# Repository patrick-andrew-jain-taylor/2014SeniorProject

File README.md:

2014SeniorProject
=================

Will contain all source files for our Glasses project

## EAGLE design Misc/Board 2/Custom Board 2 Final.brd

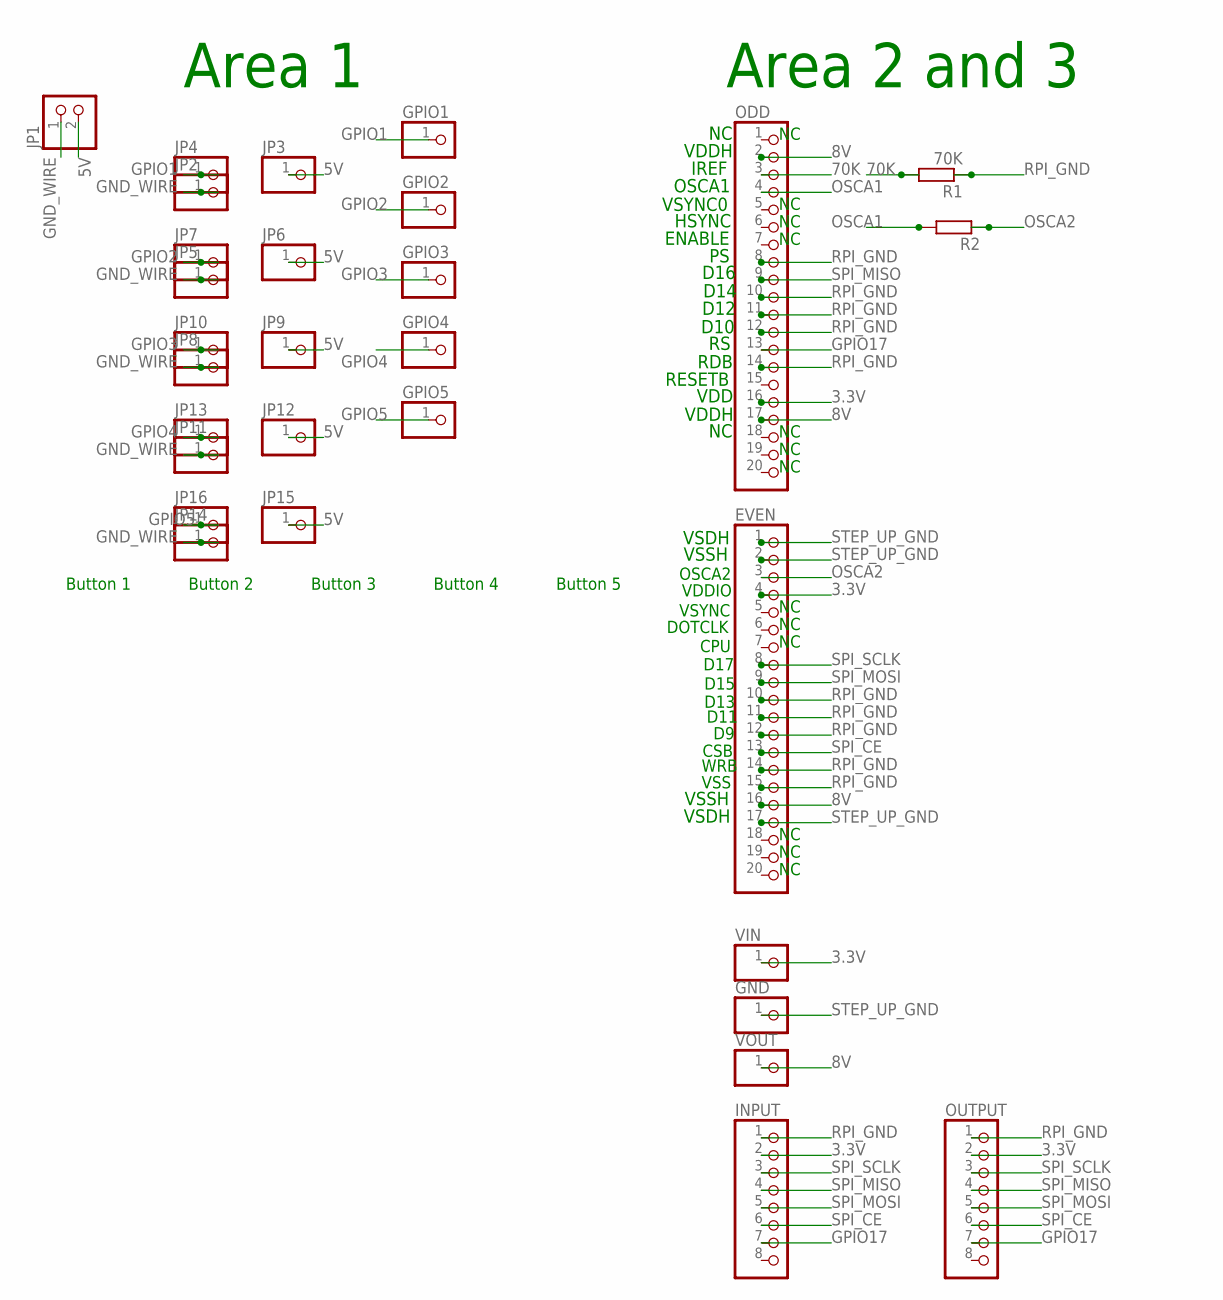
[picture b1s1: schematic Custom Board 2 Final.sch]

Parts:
EVEN: PINHD-1X20; 1X20
GND: PINHD-1X1; 1X01
GPIO1, GPIO2, GPIO3, GPIO4, GPIO5: PINHD-1X1; 1X01
INPUT: PINHD-1X8; 1X08
JP1: PINHD-1X2; 1X02
JP2, JP3, JP4, JP5, JP6, JP7, JP8, JP9, JP10, JP11, JP12, JP13, JP14, JP15, JP16: PINHD-1X1; 1X01
ODD: PINHD-1X20; 1X20
OUTPUT: PINHD-1X8; 1X08
R1: 70K; 0204/7
R2: R-EU_0204/7; 0204/7
VIN: PINHD-1X1; 1X01
VOUT: PINHD-1X1; 1X01

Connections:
3.3V: EVEN.4, INPUT.2, ODD.16, OUTPUT.2, VIN.1
5V: JP1.2, JP3.1, JP6.1, JP9.1, JP12.1, JP15.1
8V: EVEN.16, ODD.2, ODD.17, VOUT.1
70K: ODD.3, R1.2
GND_WIRE: JP1.1, JP2.1, JP5.1, JP8.1, JP11.1, JP14.1
GPIO1: GPIO1.1, JP4.1
GPIO2: GPIO2.1, JP7.1
GPIO3: GPIO3.1, JP10.1
GPIO4: GPIO4.1, JP13.1
GPIO5: GPIO5.1, JP16.1
GPIO17: INPUT.7, ODD.13, OUTPUT.7
OSCA1: ODD.4, R2.2
OSCA2: EVEN.3, R2.1
RPI_GND: EVEN.10, EVEN.11, EVEN.12, EVEN.14, EVEN.15, INPUT.1, ODD.8, ODD.10, ODD.11, ODD.12, ODD.14, OUTPUT.1, R1.1
SPI_CE: EVEN.13, INPUT.6, OUTPUT.6
SPI_MISO: INPUT.4, ODD.9, OUTPUT.4
SPI_MOSI: EVEN.9, INPUT.5, OUTPUT.5
SPI_SCLK: EVEN.8, INPUT.3, OUTPUT.3
STEP_UP_GND: EVEN.1, EVEN.2, EVEN.17, GND.1

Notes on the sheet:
Area 1
Area 2 and 3
VSDH
VDDH
VSSH
IREF
OSCA1
VSYNC0
HSYNC
ENABLE
D16
D14
D12
D10
RDB
RESETB
VDD
OSCA2
VDDIO
VSYNC
DOTCLK
CPU
D17
D15
D13
D11
CSB
WRB
VSS
Button 1
Button 2
Button 3
Button 4
Button 5

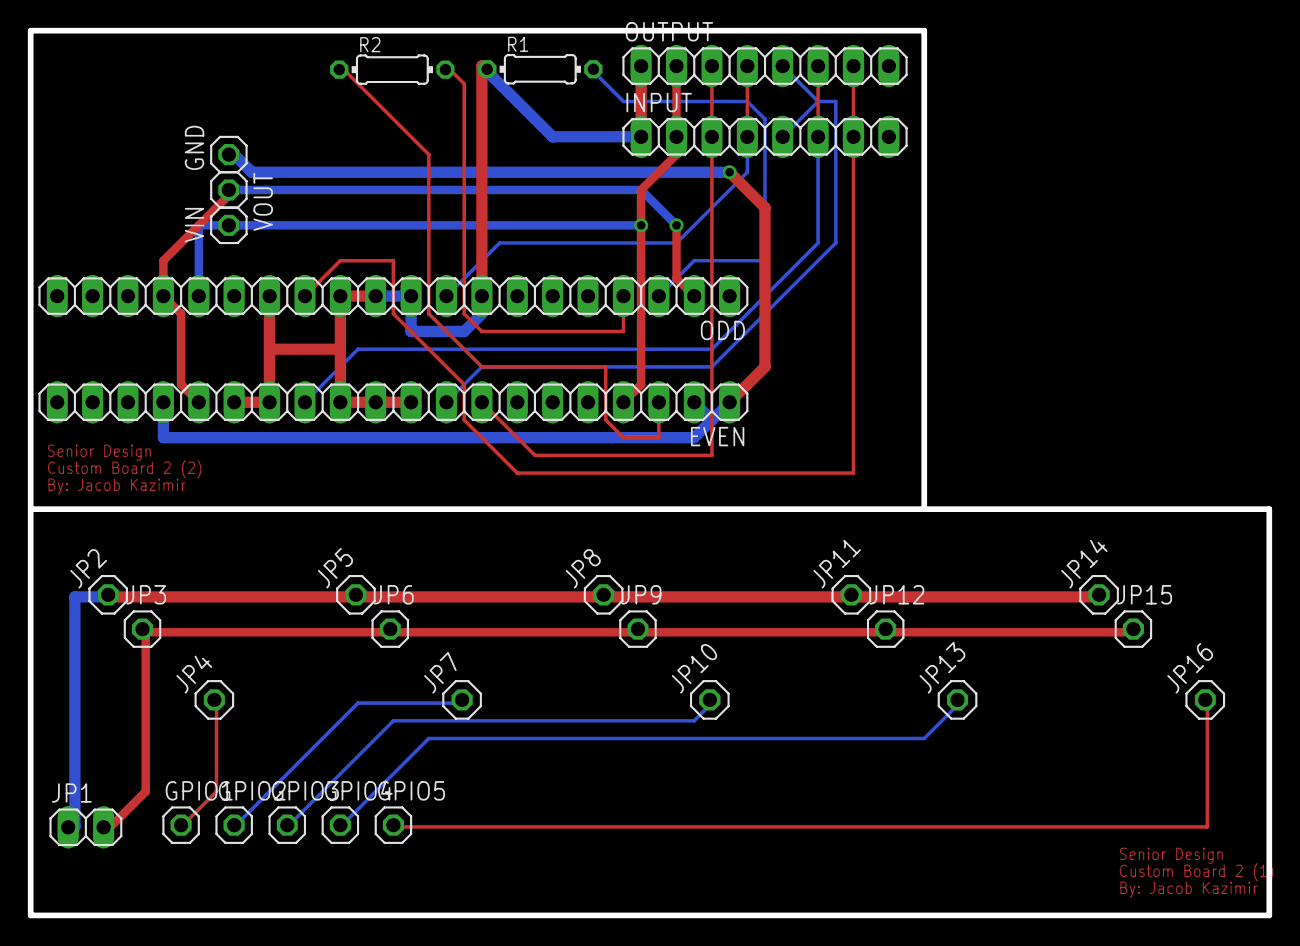
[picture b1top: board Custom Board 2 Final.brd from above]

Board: 2 copper layers, 88.9 x 63.5 mm, 30 parts (0 on the bottom side), 19 nets.

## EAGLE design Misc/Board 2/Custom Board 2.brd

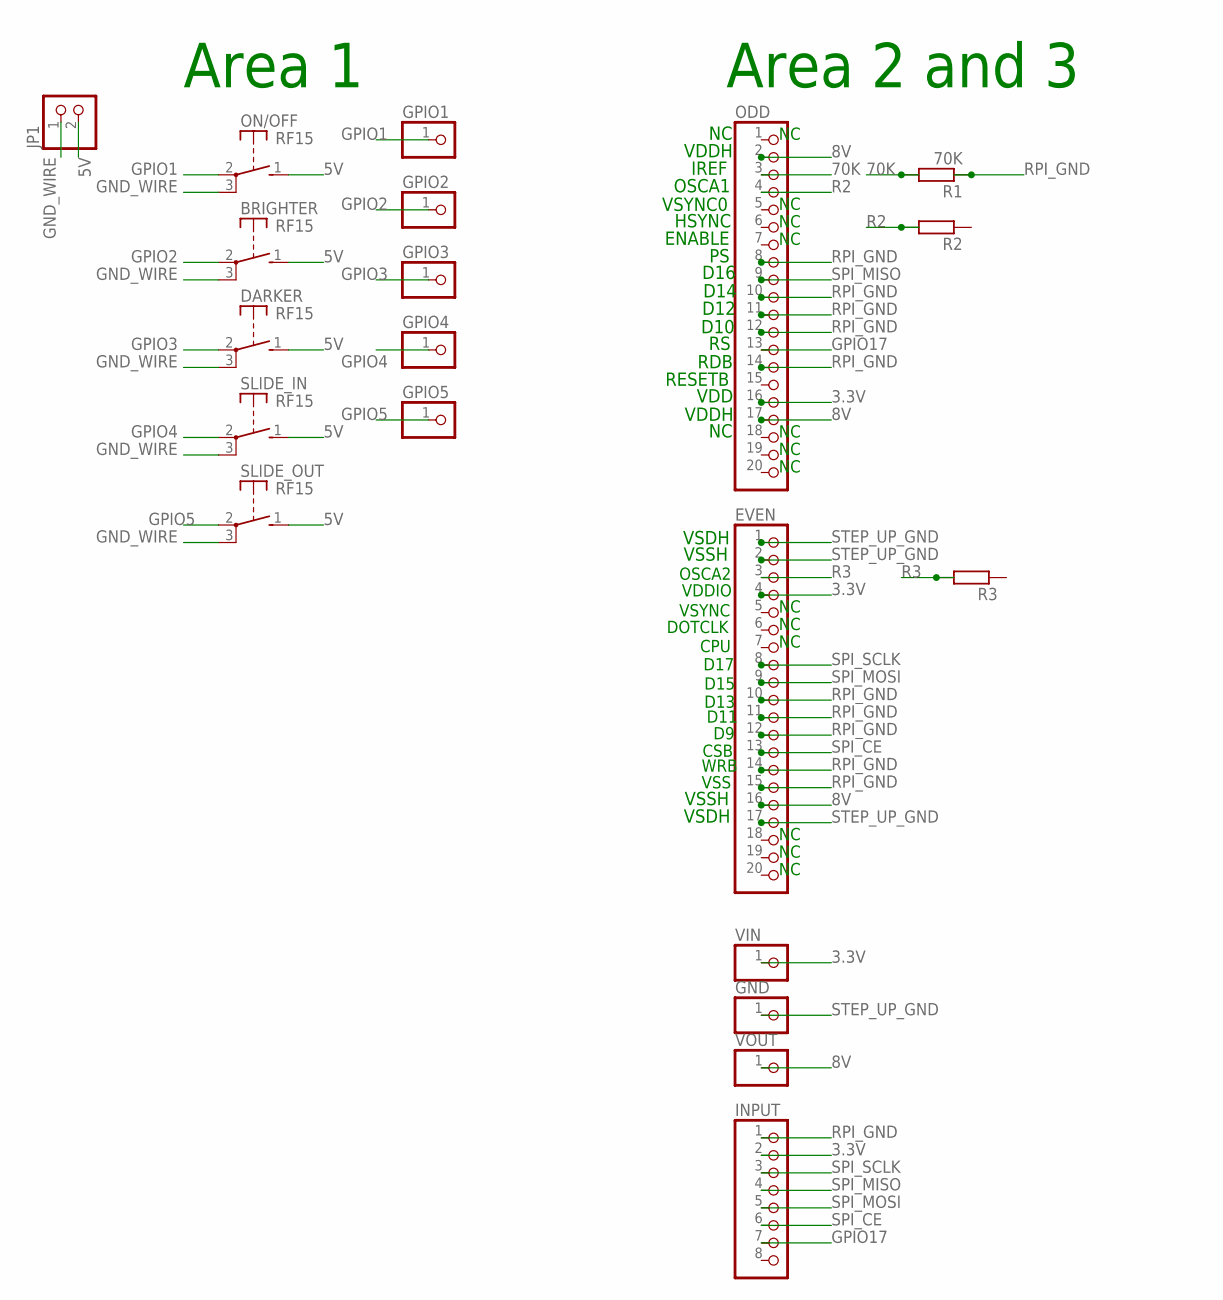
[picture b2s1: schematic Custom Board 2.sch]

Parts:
BRIGHTER: RF15
DARKER: RF15
EVEN: PINHD-1X20; 1X20
GND: PINHD-1X1; 1X01
GPIO1, GPIO2, GPIO3, GPIO4, GPIO5: PINHD-1X1; 1X01
INPUT: PINHD-1X8; 1X08
JP1: PINHD-1X2; 1X02
ODD: PINHD-1X20; 1X20
ON/OFF: RF15
R1: 70K; 0204/7
R2, R3: R-EU_0204/7; 0204/7
SLIDE_IN: RF15
SLIDE_OUT: RF15
VIN: PINHD-1X1; 1X01
VOUT: PINHD-1X1; 1X01

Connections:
3.3V: EVEN.4, INPUT.2, ODD.16, VIN.1
5V: BRIGHTER.1 (S), DARKER.1 (S), JP1.2, ON/OFF.1 (S), SLIDE_IN.1 (S), SLIDE_OUT.1 (S)
8V: EVEN.16, ODD.2, ODD.17, VOUT.1
70K: ODD.3, R1.2
GND_WIRE: BRIGHTER.3, DARKER.3, JP1.1, ON/OFF.3, SLIDE_IN.3, SLIDE_OUT.3
GPIO1: GPIO1.1, ON/OFF.2
GPIO2: BRIGHTER.2, GPIO2.1
GPIO3: DARKER.2, GPIO3.1
GPIO4: GPIO4.1, SLIDE_IN.2
GPIO5: GPIO5.1, SLIDE_OUT.2
GPIO17: INPUT.7, ODD.13
R2: ODD.4, R2.2
R3: EVEN.3, R3.2
RPI_GND: EVEN.10, EVEN.11, EVEN.12, EVEN.14, EVEN.15, INPUT.1, ODD.8, ODD.10, ODD.11, ODD.12, ODD.14, R1.1
SPI_CE: EVEN.13, INPUT.6
SPI_MISO: INPUT.4, ODD.9
SPI_MOSI: EVEN.9, INPUT.5
SPI_SCLK: EVEN.8, INPUT.3
STEP_UP_GND: EVEN.1, EVEN.2, EVEN.17, GND.1

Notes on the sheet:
Area 1
Area 2 and 3
VSDH
VDDH
VSSH
IREF
OSCA1
VSYNC0
HSYNC
ENABLE
D16
D14
D12
D10
RDB
RESETB
VDD
OSCA2
VDDIO
VSYNC
DOTCLK
CPU
D17
D15
D13
D11
CSB
WRB
VSS

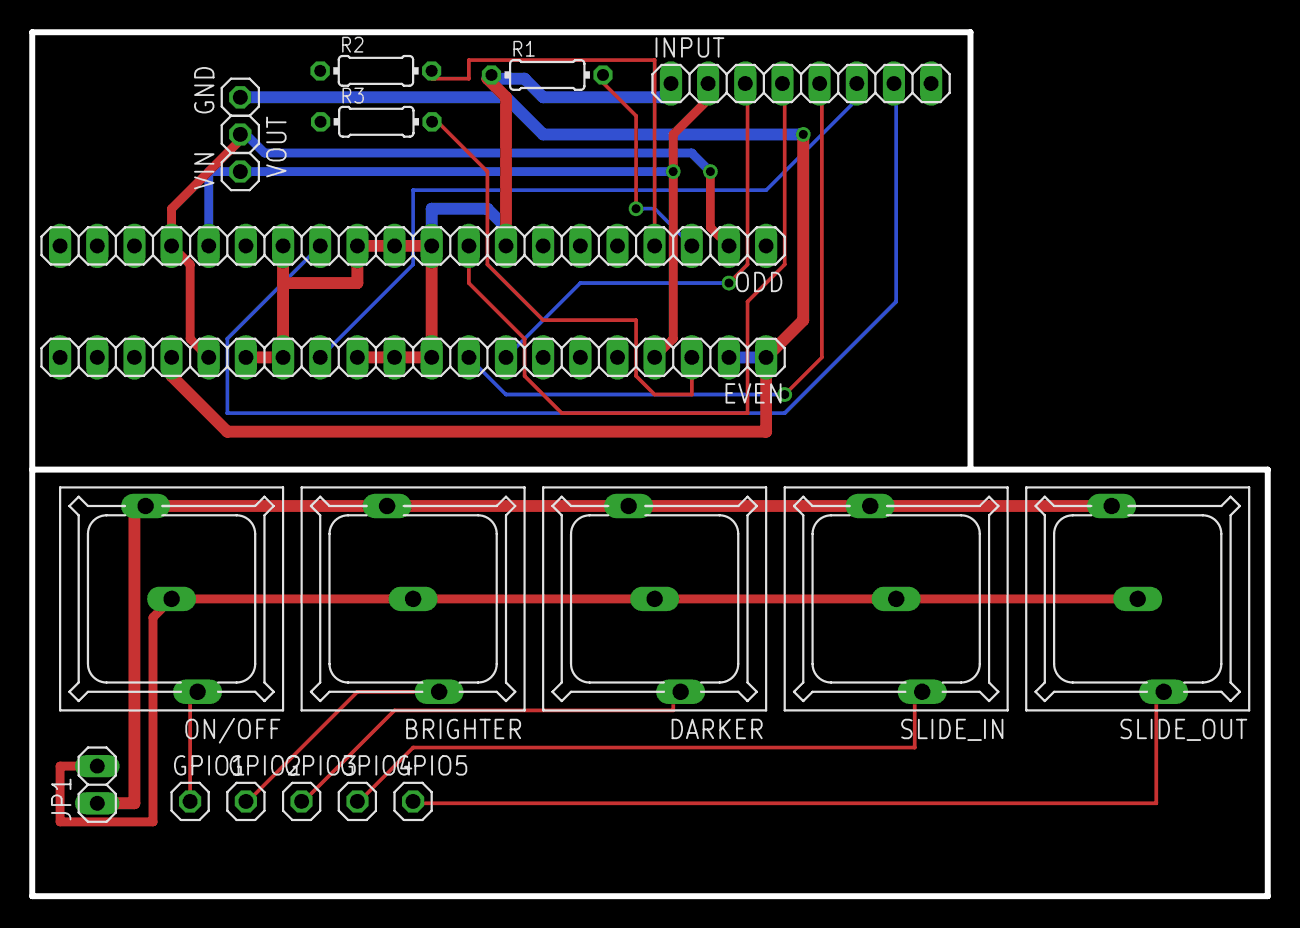
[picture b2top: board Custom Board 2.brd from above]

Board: 2 copper layers, 84.5 x 59.1 mm, 20 parts (0 on the bottom side), 19 nets.

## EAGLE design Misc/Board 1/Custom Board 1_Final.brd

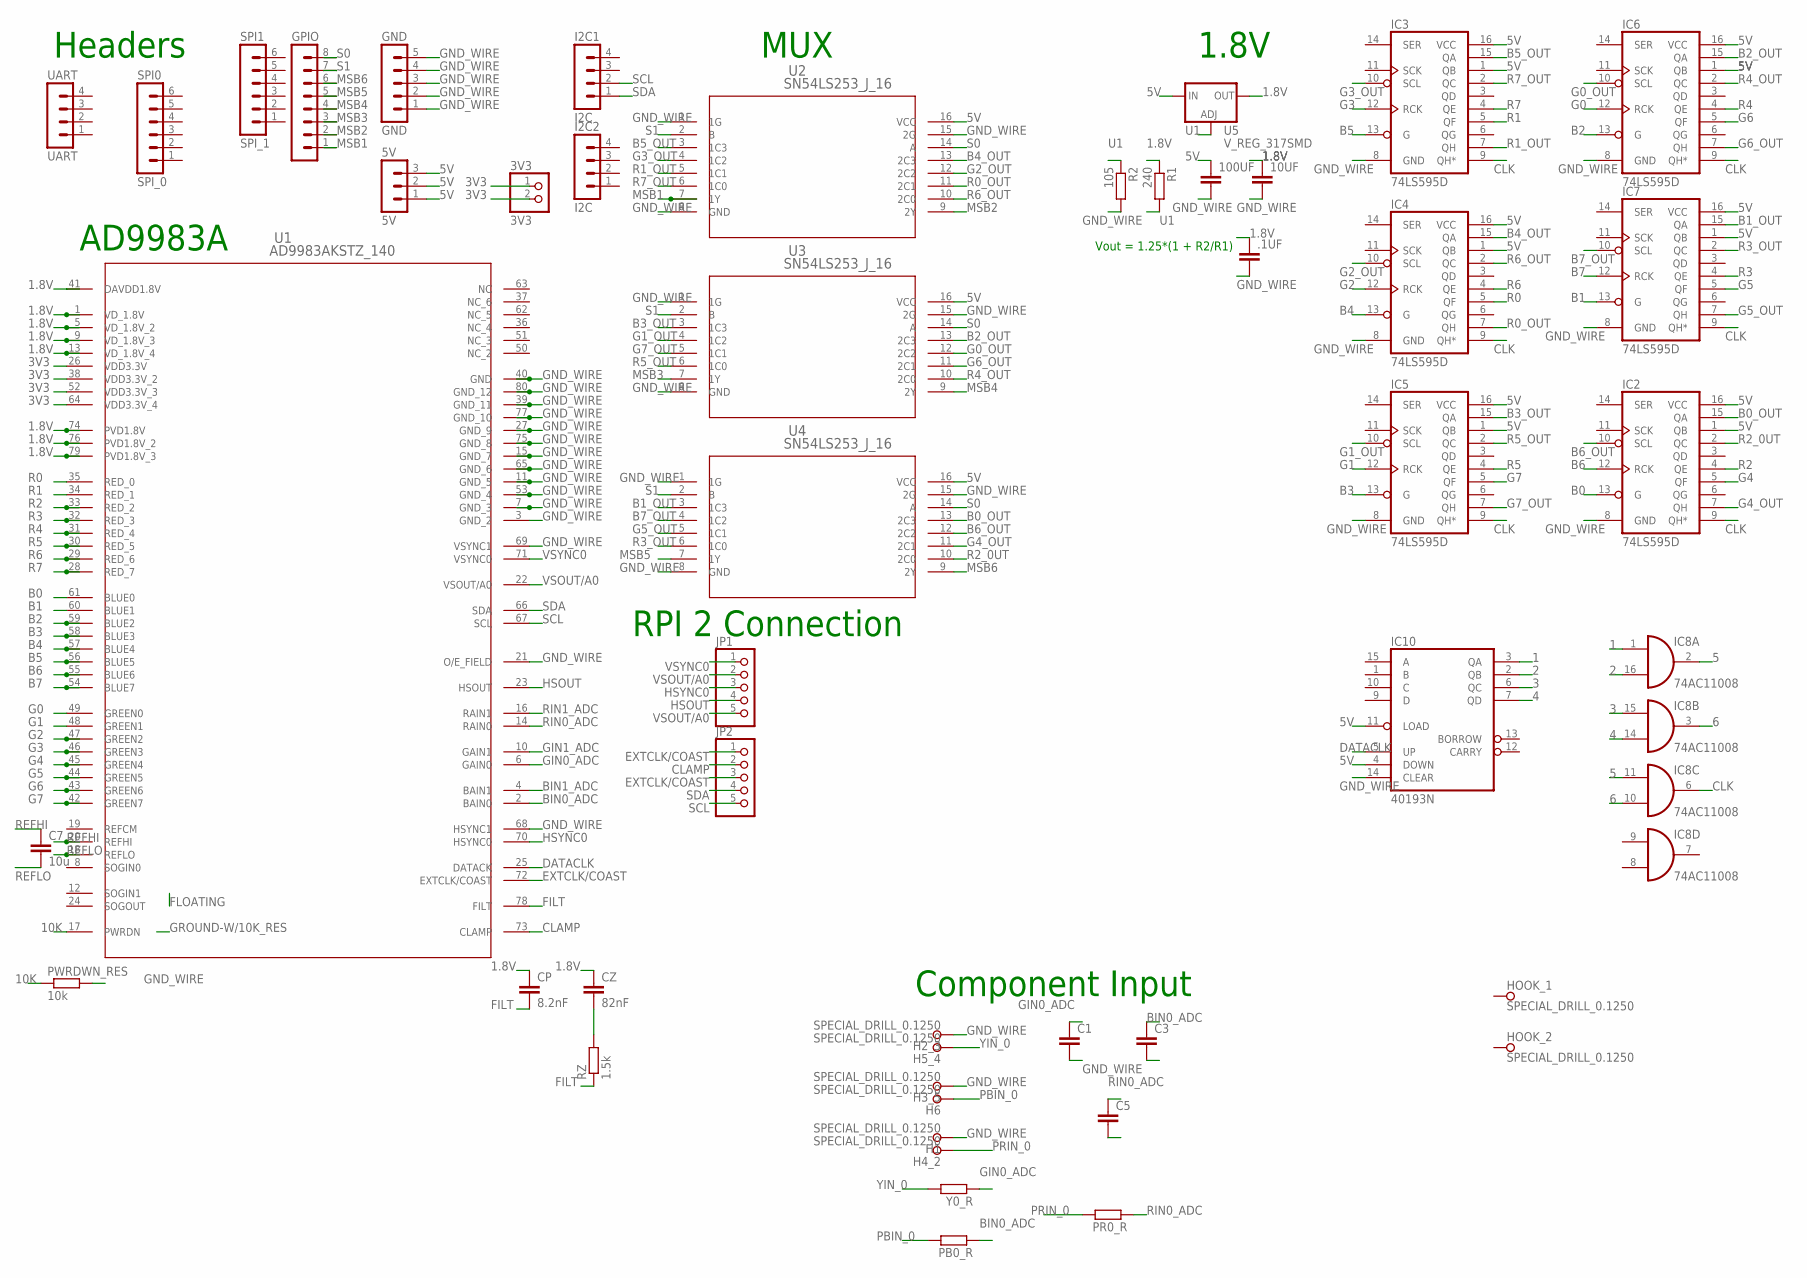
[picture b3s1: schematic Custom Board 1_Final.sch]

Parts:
3V3: 3V3; 1X02
5V: 5V; MA03-1
10UF, 100UF, .1UF: C2.5/5; C2.5-5
C1, C3, C5: C2.5/5; C2.5-5
C7: 10u; C2.5-5
CP: 8.2nF; C2.5-5
CZ: 82nF; C2.5-5
GND: GND; MA05-1
GPIO: MA08-1
H1, H2_3, H3_5, H4_2, H5_4, H6: SPECIAL_DRILL_0.1250; PAD_0.1250
HOOK_1, HOOK_2: SPECIAL_DRILL_0.1250; PAD_0.1250
I2C1, I2C2: I2C; MA04-1
IC2, IC3, IC4, IC5, IC6, IC7: 74LS595D; SO16
IC8: 74AC11008; DIL16
IC10: 40193N; DIL16
JP1, JP2: PINHD-1X5; 1X05
PB0_R: R0204/7; 0204/7
PR0_R: R0204/7; 0204/7
PWRDWN_RES: 10k; 0204/7
R1: 240; 0204/7
R2: 105; 0204/7
RZ: 1.5k; 0204/7
SPI0: SPI_0; MA06-1
SPI1: SPI_1; MA06-1
U1: AD9983AKSTZ_140; ST_80_2
U2, U3, U4: SN54LS253_J_16; J16
U5: V_REG_317SMD; SOT223
UART: UART; MA04-1
Y0_R: R0204/7; 0204/7

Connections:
1: IC8.1 (I0), IC10.3 (QA)
1.8V: 10UF.1, .1UF.1, CP.1, CZ.1, R1.1, U1.1 (VD_1.8V), U1.5 (VD_1.8V_2), U1.9 (VD_1.8V_3), U1.13 (VD_1.8V_4), U1.41 (DAVDD1.8V), U1.74 (PVD1.8V), U1.76 (PVD1.8V_2), U1.79 (PVD1.8V_3), U5.2 (OUT)
2: IC8.16 (I1), IC10.2 (QB)
3: IC8.15 (I0), IC10.6 (QC)
3V3: 3V3.1, 3V3.2, U1.26 (VDD3.3V), U1.38 (VDD3.3V_2), U1.52 (VDD3.3V_3), U1.64 (VDD3.3V_4)
4: IC8.14 (I1), IC10.7 (QD)
5: IC8.2 (O), IC8.11 (I0)
5V: 5V.1, 5V.2, 5V.3, 100UF.1, IC2.1 (QB), IC2.16 (VCC), IC3.1 (QB), IC3.16 (VCC), IC4.1 (QB), IC4.16 (VCC), IC5.1 (QB), IC5.16 (VCC), IC6.1 (QB), IC6.16 (VCC), IC7.1 (QB), IC7.16 (VCC), IC10.4 (DOWN), IC10.11 (LOAD), U2.16 (VCC), U3.16 (VCC), U4.16 (VCC), U5.3 (IN)
6: IC8.3 (O), IC8.10 (I1)
10K: PWRDWN_RES.1, U1.17 (PWRDN)
B0: IC2.13 (G), U1.61 (BLUE0)
B0_OUT: IC2.15 (QA), U4.13 (2C3)
B1: IC7.13 (G), U1.60 (BLUE1)
B1_OUT: IC7.15 (QA), U4.3 (1C3)
B2: IC6.13 (G), U1.59 (BLUE2)
B2_OUT: IC6.15 (QA), U3.13 (2C3)
B3: IC5.13 (G), U1.58 (BLUE3)
B3_OUT: IC5.15 (QA), U3.3 (1C3)
B4: IC4.13 (G), U1.57 (BLUE4)
B4_OUT: IC4.15 (QA), U2.13 (2C3)
B5: IC3.13 (G), U1.56 (BLUE5)
B5_OUT: IC3.15 (QA), U2.3 (1C3)
B6: IC2.12 (RCK), U1.55 (BLUE6)
B6_OUT: IC2.10 (SCL), U4.12 (2C2)
B7: IC7.12 (RCK), U1.54 (BLUE7)
B7_OUT: IC7.10 (SCL), U4.4 (1C2)
BIN0_ADC: C3.1, PB0_R.1, U1.2 (BAIN0)
BIN1_ADC: U1.4 (BAIN1)
CLAMP: JP2.2, U1.73 (CLAMP)
CLK: IC2.9 (QH*), IC3.9 (QH*), IC4.9 (QH*), IC5.9 (QH*), IC6.9 (QH*), IC7.9 (QH*), IC8.6 (O)
DATACLK: IC10.5 (UP), U1.25 (DATACK)
EXTCLK/COAST: JP2.1, JP2.3, U1.72 (EXTCLK/COAST)
FILT: CP.2, RZ.1, U1.78 (FILT)
G0: IC6.12 (RCK), U1.49 (GREEN0)
G0_OUT: IC6.10 (SCL), U3.12 (2C2)
G1: IC5.12 (RCK), U1.48 (GREEN1)
G1_OUT: IC5.10 (SCL), U3.4 (1C2)
G2: IC4.12 (RCK), U1.47 (GREEN2)
G2_OUT: IC4.10 (SCL), U2.12 (2C2)
G3: IC3.12 (RCK), U1.46 (GREEN3)
G3_OUT: IC3.10 (SCL), U2.4 (1C2)
G4: IC2.5 (QF), U1.45 (GREEN4)
G4_OUT: IC2.7 (QH), U4.11 (2C1)
G5: IC7.5 (QF), U1.44 (GREEN5)
G5_OUT: IC7.7 (QH), U4.5 (1C1)
G6: IC6.5 (QF), U1.43 (GREEN6)
G6_OUT: IC6.7 (QH), U3.11 (2C1)
G7: IC5.5 (QF), U1.42 (GREEN7)
G7_OUT: IC5.7 (QH), U3.5 (1C1)
GIN0_ADC: C1.1, U1.6 (GAIN0), Y0_R.1
GIN1_ADC: U1.10 (GAIN1)
GND: IC8.4 (GND), IC8.5 (GND)
GND_WIRE: 10UF.2, 100UF.2, .1UF.2, C1.2, C3.2, C5.2, GND.1, GND.2, GND.3, GND.4, GND.5, H1.1, H2_3.1, H3_5.1, IC2.8 (GND), IC3.8 (GND), IC4.8 (GND), IC5.8 (GND), IC6.8 (GND), IC7.8 (GND), IC10.14 (CLEAR), PWRDWN_RES.2, R2.2, U1.3 (GND_2), U1.7 (GND_3), U1.11 (GND_5), U1.15 (GND_7), U1.21 (O/E_FIELD), U1.27 (GND_9), U1.39 (GND_11), U1.40 (GND), U1.53 (GND_4), U1.65 (GND_6), U1.68 (HSYNC1), U1.69 (VSYNC1), U1.75 (GND_8), U1.77 (GND_10), U1.80 (GND_12), U2.1 (1G), U2.8 (GND), U2.15 (2G), U3.1 (1G), U3.8 (GND), U3.15 (2G), U4.1 (1G), U4.8 (GND), U4.15 (2G)
HSOUT: JP1.4, U1.23 (HSOUT)
HSYNC0: JP1.3, U1.70 (HSYNC0)
MSB1: GPIO.1, U2.7 (1Y)
MSB2: GPIO.2, U2.9 (2Y)
MSB3: GPIO.3, U3.7 (1Y)
MSB4: GPIO.4, U3.9 (2Y)
MSB5: GPIO.5, U4.7 (1Y)
MSB6: GPIO.6, U4.9 (2Y)
unnamed: CZ.2, RZ.2
PBIN_0: H6.1, PB0_R.2
PRIN_0: H4_2.1, PR0_R.2
R0: IC4.5 (QF), U1.35 (RED_0)
R0_OUT: IC4.7 (QH), U2.11 (2C1)
R1: IC3.5 (QF), U1.34 (RED_1)
R1_OUT: IC3.7 (QH), U2.5 (1C1)
R2: IC2.4 (QE), U1.33 (RED_2)
R2_0UT: IC2.2 (QC), U4.10 (2C0)
R3: IC7.4 (QE), U1.32 (RED_3)
R3_OUT: IC7.2 (QC), U4.6 (1C0)
R4: IC6.4 (QE), U1.31 (RED_4)
R4_OUT: IC6.2 (QC), U3.10 (2C0)
R5: IC5.4 (QE), U1.30 (RED_5)
R5_OUT: IC5.2 (QC), U3.6 (1C0)
R6: IC4.4 (QE), U1.29 (RED_6)
R6_OUT: IC4.2 (QC), U2.10 (2C0)
R7: IC3.4 (QE), U1.28 (RED_7)
R7_OUT: IC3.2 (QC), U2.6 (1C0)
REFHI: C7.1, U1.20 (REFHI)
REFLO: C7.2, U1.18 (REFLO)
RIN0_ADC: C5.1, PR0_R.1, U1.14 (RAIN0)
RIN1_ADC: U1.16 (RAIN1)
S0: GPIO.8, U2.14 (A), U3.14 (A), U4.14 (A)
S1: GPIO.7, U2.2 (B), U3.2 (B), U4.2 (B)
SCL: I2C1.2, JP2.5, U1.67 (SCL)
SDA: I2C1.1, JP2.4, U1.66 (SDA)
U1: R1.2, R2.1, U5.1 (ADJ)
VCC: IC8.12 (VCC), IC8.13 (VCC)
VDD: IC10.16 (VDD)
VSOUT/A0: JP1.2, JP1.5, U1.22 (VSOUT/A0)
VSS: IC10.8 (VSS)
VSYNC0: JP1.1, U1.71 (VSYNC0)
YIN_0: H5_4.1, Y0_R.2

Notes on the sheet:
Headers
AD9983A
MUX
Component Input
1.8V
Vout = 1.25*(1 + R2/R1)
RPI 2 Connection

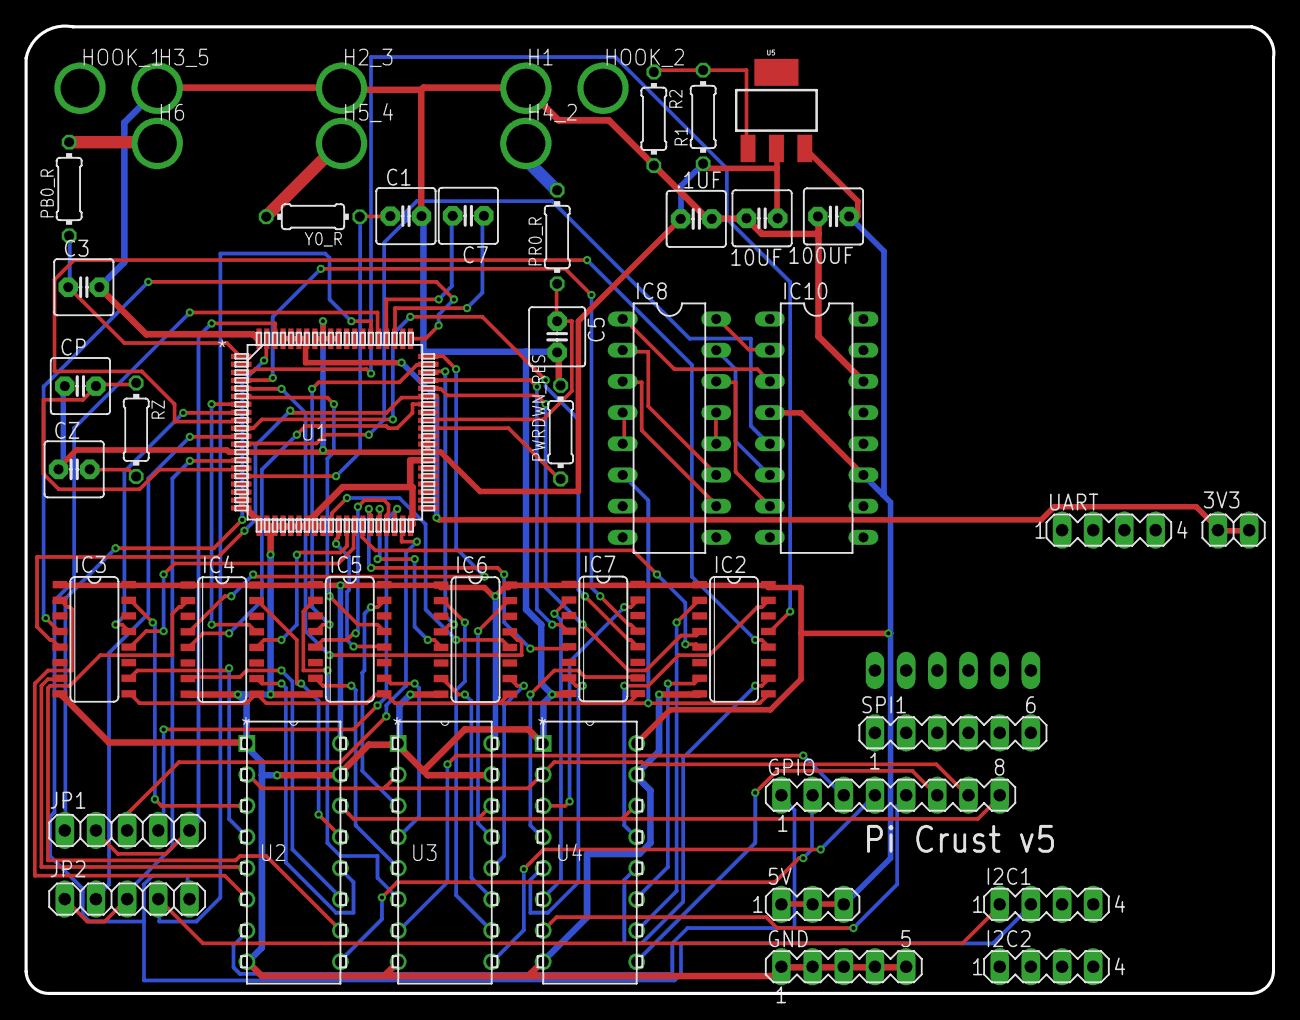
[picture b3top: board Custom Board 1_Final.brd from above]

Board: 2 copper layers, 101.6 x 78.8 mm, 48 parts (1 on the bottom side), 90 nets.

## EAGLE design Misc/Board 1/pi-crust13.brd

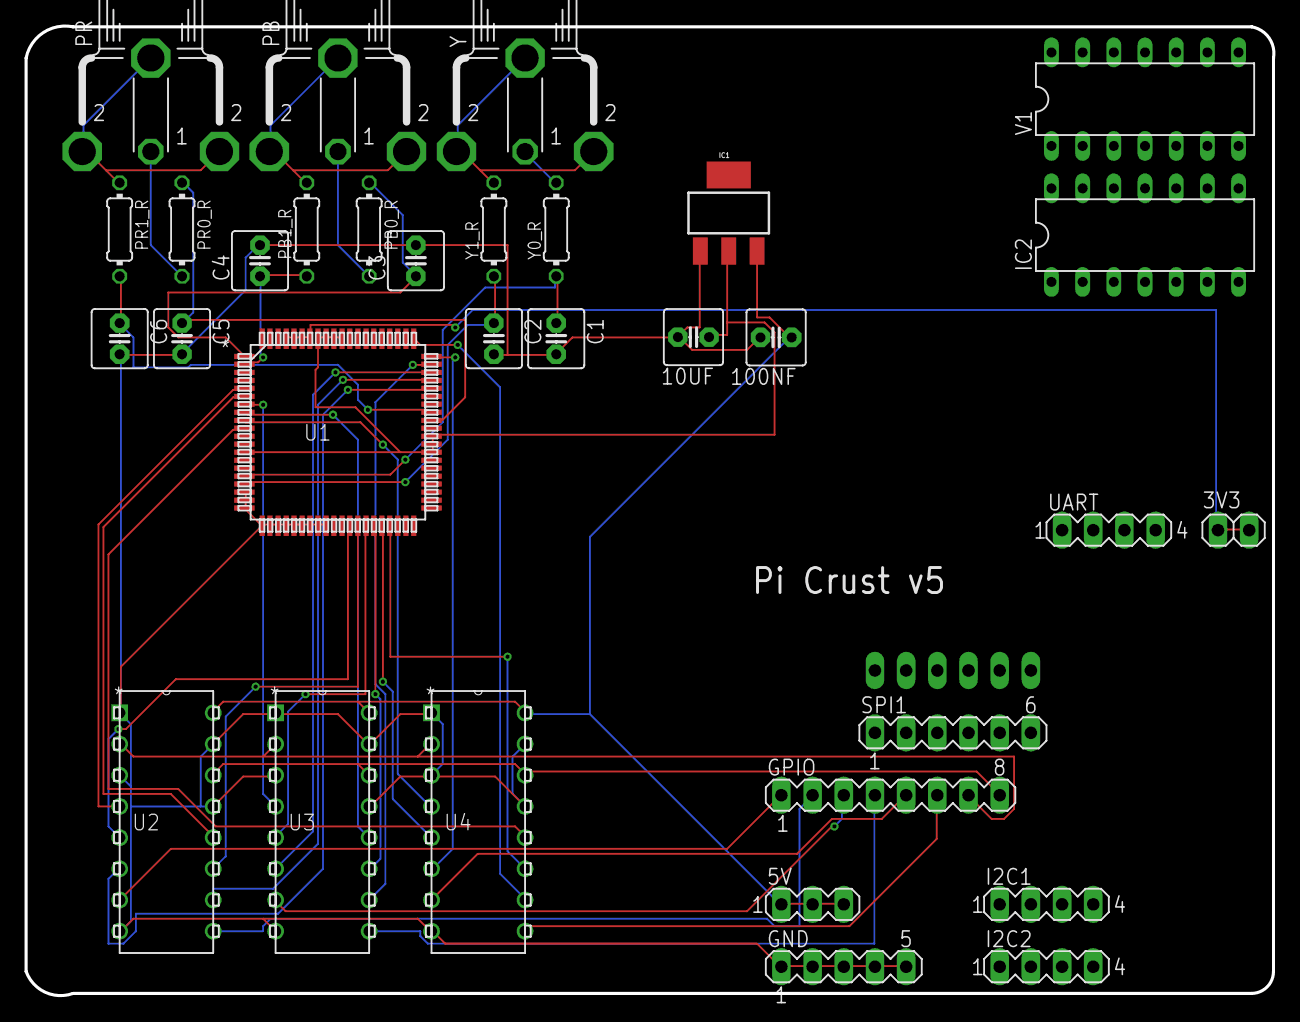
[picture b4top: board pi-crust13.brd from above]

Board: 2 copper layers, 101.6 x 79.0 mm, 33 parts (1 on the bottom side), 42 nets.

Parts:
3V3: 3V3; 1X02
5V: 5V; MA03-1
10UF, 100NF: C2.5-5
C1, C2, C3, C4, C5, C6: C2.5-5
GND: GND; MA05-1
GPIO: MA08-1
I2C1, I2C2: I2C; MA04-1
IC1: SOT223
IC2: 74AC74N; DIL14
PB: TOBU3
PB0_R, PB1_R: 0204/7
PR: TOBU3
PR0_R, PR1_R: 0204/7
SPI0: SPI_0; MA06-1
SPI1: SPI_1; MA06-1
U1: AD9983AKSTZ_140; ST_80_2
U2, U3, U4: SN54LS253_J_16; J16
UART: UART; MA04-1
V1: 7474N; DIL14
Y: TOBU3
Y0_R, Y1_R: 0204/7

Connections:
1.8V: 10UF.1, IC1.2, U1.1, U1.5, U1.9, U1.13, U1.41, U1.74, U1.76, U1.79
3V3: 3V3.1, 3V3.2, U1.26, U1.38, U1.52, U1.64
5V: 5V.1, 5V.2, 5V.3, 100NF.1, IC1.3, U2.16, U3.16, U4.16
12: U1.58, U2.12
B1: U1.59, U2.4
B3: U1.57, U3.4
B4: U1.56, U3.12
B5: U1.55, U4.4
B6: U1.54, U4.12
BIN0_ADC: C3.1, PB0_R.1, U1.2
BIN1_ADC: C4.1, PB1_R.1, U1.4
G1: U1.47, U2.5
G2: U1.46, U2.11
G3: U1.45, U3.5
G4: U1.44, U3.11
G5: U1.43, U4.5
G6: U1.42, U4.11
GIN0_ADC: C1.1, U1.6, Y0_R.1
GIN1_ADC: C2.1, U1.10, Y1_R.1
GND_WIRE: 10UF.2, 100NF.2, C1.2, C2.2, C3.2, C4.2, C5.2, C6.2, GND.1, GND.2, GND.3, GND.4, GND.5, IC1.1, U1.3, U1.7, U1.11, U1.15, U1.27, U1.39, U1.40, U1.53, U1.65, U1.75, U1.77, U1.80, U2.1, U2.3, U2.8, U2.13, U2.15, U3.1, U3.3, U3.8, U3.13, U3.15, U4.1, U4.3, U4.8, U4.13, U4.15
MSB1: GPIO.1, U2.7
MSB2: GPIO.2, U2.9
MSB3: GPIO.3, U3.7
MSB4: GPIO.4, U3.9
MSB5: GPIO.5, U4.7
MSB6: GPIO.6, U4.9
PBIN_0: PB.1, PB0_R.2
PBIN_1: PB.2, PB.2@1, PB.2@2, PB1_R.2
PRIN_0: PR.1, PR0_R.2
PRIN_1: PR.2, PR.2@1, PR.2@2, PR1_R.1
R1: U1.33, U2.6
R2: U1.32, U2.10
R3: U1.31, U3.6
R4: U1.30, U3.10
R5: U1.29, U4.6
R6: U1.28, U4.10
RIN0_ADC: C5.1, PR0_R.1, U1.14
RIN1_ADC: C6.1, PR1_R.2, U1.16
S0: GPIO.8, U2.14, U3.14, U4.14
S1: GPIO.7, U2.2, U3.2, U4.2
YIN_0: Y.1, Y0_R.2
YIN_1: Y.2, Y.2@1, Y.2@2, Y1_R.2

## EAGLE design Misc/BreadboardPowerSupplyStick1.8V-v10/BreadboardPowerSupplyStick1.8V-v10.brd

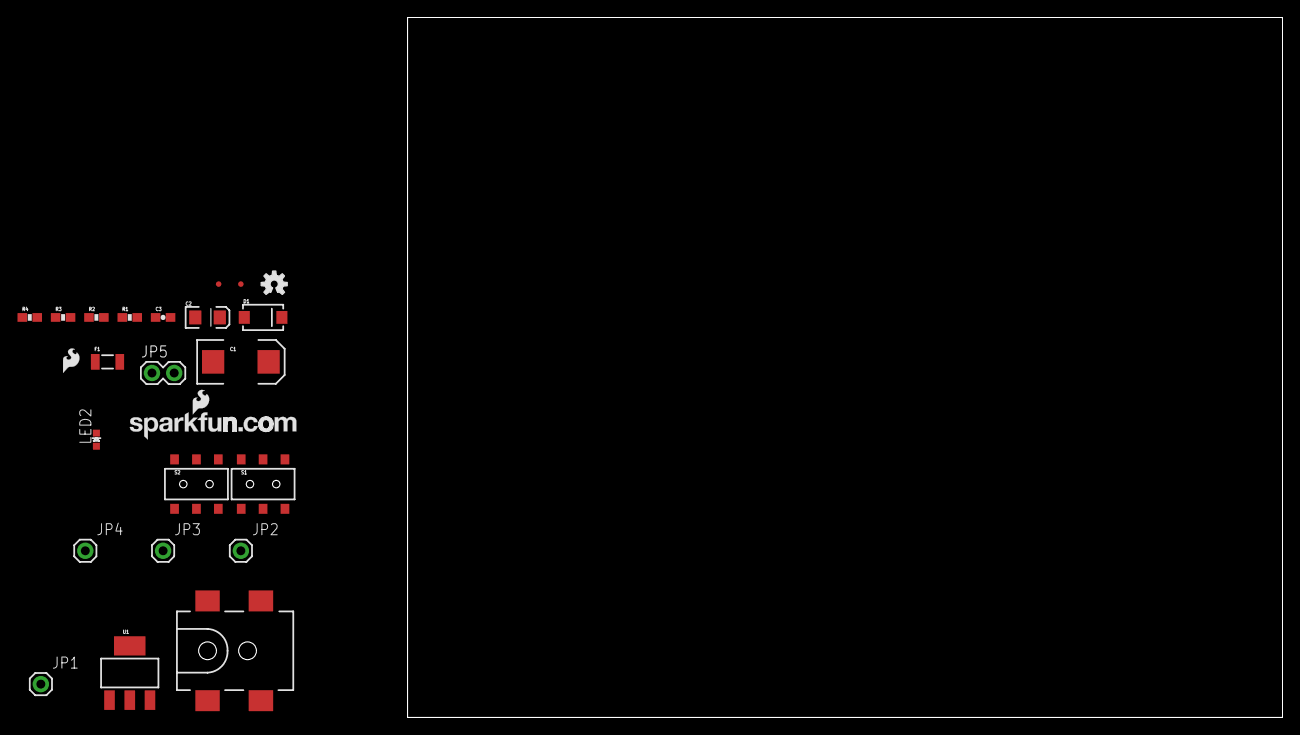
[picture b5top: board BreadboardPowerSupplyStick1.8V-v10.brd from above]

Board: 2 copper layers, 100.0 x 80.0 mm, 24 parts (0 on the bottom side), 9 nets, no tracks yet.

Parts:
C1: 100uF; EIA7343
C2: 10uF; EIA3216
C3: 0.1uF; 0603-CAP
D1: 1N4001; SMA-DIODE
F1: PTCSMD; PTC-1206
J1: POWER_JACKSMD; POWER_JACK_SMD
JP1, JP2, JP3, JP4: M01PTH; 1X01
JP5: 1X02
JP6, JP7: FIDUCIALUFIDUCIAL; MICRO-FIDUCIAL
LED2: Power; LED-0603
R1, R4: 240; 0603-RES
R2: 105; 0603-RES
R3: 287; 0603-RES
S1: On/Off; AYZ0202
S2: Voltage; AYZ0202
U1: V_REG_317SMD; SOT223
U$1: LOGO-SFESK; SFE-LOGO-FLAME
U$2: LOGO-SFENEW; SFE-NEW-WEBLOGO
U$6: OSHW-LOGOS; OSHW-LOGO-S

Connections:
GND: C1.C, C2.C, C3.2, J1.GND, J1.P$4, JP1.1, JP4.1, JP5.2, LED2.C, R3.1, S2.3
unnamed: D1.C, F1.1
unnamed: D1.A, S1.1, S1.4
unnamed: R2.1, R3.2, S2.2
unnamed: R1.1, R2.2, U1.1
unnamed: LED2.A, R4.1
RAW: C1.A, F1.2, U1.3
VCC: C2.A, C3.1, JP2.1, JP3.1, R1.2, R4.2, U1.2
VIN: J1.VIN0, JP5.1, S1.2, S1.5

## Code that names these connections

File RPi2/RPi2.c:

#include <sys/socket.h>
#include <netinet/in.h>
#include <arpa/inet.h>
#include <stdio.h>
#include <stdlib.h>
#include <unistd.h>
#include <errno.h>
#include <string.h>
#include <sys/types.h>
#include <pthread.h>
#include <linux/i2c-dev.h>
#include "WiringPi/wiringPi/wiringPi.h"
#include "WiringPi/wiringPi/wiringPiI2C.h"
 
int RPi2Setup(void)
{
	wiringPiSetup();
	//set modes
	pinMode(7, OUTPUT);	// GPIO 4  -- HSYNC0
	pinMode(0, INPUT);	// GPIO 17 -- HSOUT
	pinMode(1, OUTPUT);	// GPIO 18 -- VSYNC0
	pinMode(2, INPUT);	// GPIO 21 -- VSOUT
	pinMode(3, OUTPUT);	// GPIO 22 -- A0
	pinMode(4, INPUT);	// GPIO 23 -- EXTCLK
	pinMode(5, OUTPUT);	// GPIO 24 -- CLAMP
	pinMode(6, OUTPUT);	// GPIO 25 -- COAST
	//set clocks
	digitalWrite(7, HIGH);
	digitalWrite(1, HIGH);
	//initalize serial
	/*wiringPiI2CSetup(0x4C); //unsure what device ID is for now, will test
	//set PLL to 800
	wiringPiI2CWriteReg16(0x4C, 0x01,0x2800); //PLL to 640
	wiringPiI2CWriteReg8(0x4C, 0x03, 0x28); //VCO/CPMP*/
	return 0;
}
 
int socketServer(void)
{
  int listenfd = 0;//,connfd = 0;
  
  struct sockaddr_in serv_addr;
 
  char recvBuff[2];  
  //int numrv;  
 
  listenfd = socket(AF_INET, SOCK_STREAM, 0);
  printf("socket retrieve success\n");
  
  memset(&serv_addr, '0', sizeof(serv_addr));
  memset(recvBuff, '0', sizeof(recvBuff));
      
  serv_addr.sin_family = AF_INET;    
  serv_addr.sin_addr.s_addr = htonl(INADDR_ANY); 
  serv_addr.sin_port = htons(17350);    
 
  bind(listenfd, (struct sockaddr*)&serv_addr,sizeof(serv_addr));
  
  if(listen(listenfd, 10) == -1){
      printf("Failed to listen\n");
      return -1;
  }
  
  /*connfd = */accept(listenfd, (struct sockaddr*)NULL ,NULL); // accept awaiting request

  return 0;
}

int socketClient(void)
{
  int sockfd = 0;//,n = 0;
  char sendBuff[3];
  struct sockaddr_in serv_addr;
 
  memset(sendBuff, '0' ,sizeof(sendBuff));
  if((sockfd = socket(AF_INET, SOCK_STREAM, 0))< 0)
    {
      printf("\n Error : Could not create socket \n");
      return 1;
    }
 
  serv_addr.sin_family = AF_INET;
  serv_addr.sin_port = htons(17350);
  serv_addr.sin_addr.s_addr = inet_addr("192.168.0.101");
 
  if(connect(sockfd, (struct sockaddr *)&serv_addr, sizeof(serv_addr))<0)
    {
      printf("\n Error : Connect Failed \n");
      return 1;
    }
  //begin MUX incrementation
	uint16_t hcount = 0; //used to generate 60Hz*480 clock
	uint16_t vcount = 0; //used to generate 60Hz clock
	//basic implementation of 60Hz clock -- NOT FINAL
	while(1){//loop indefinitely
		//Check valid data first
		if (hcount < 640){ //0-639 valid data
			if ((vcount < 480)){ //0-479 valid data, hcount has a factor of 4
				//tell RPI1 data is valid
				write(sockfd, 0x00, strlen(sendBuff));
			}
		}
		write(sockfd, 0xFF, strlen(sendBuff));
		//HSYNC first
		//@660 -> HSYNC set low
		if (hcount == 660) digitalWrite(7, LOW);
		//@756 -> HSYNC set high
		else if (hcount == 756) digitalWrite(7, HIGH);
		else if (hcount == 800) {
			//VSYNC Second
			//@494 -> VSYNC set low
			if (vcount == 494) digitalWrite(1, LOW);
			//@495 -> VSYNC set high
			else if (vcount == 495) digitalWrite(1, HIGH);
			vcount = (vcount++) % 525; //increment VSYNC < 525
		}
		hcount = (hcount++ % 800); //increment HSYNC < 800
	}
  return 0;
}

int main(void)
{
	RPi2Setup();
	//pthread_t server;
	//pthread_t client;
	//pthread_create(&client, NULL, socketClient, NULL);
	//pthread_create(&server, NULL, socketServer, NULL);
	return 0;
}

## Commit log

2013-06-19 hostapd.zip added, comes from AP tutorial and is used to successfully configure the AP using Internet and DHCP. Next step will be configuring it for local with DHCP.
2013-06-19 will be used to test DHCP settings.
2014-02-08 Basic Python files for TCP and UDP Sending and Receiving
2014-02-08 This new folder contains the Wireless Access Point Tutorial, which will allow for the Raspberry Pi's to connect to one another, which is necessary for data transfer.
2014-02-11 hostapd.conf has been updated with the appropriate values for our secure wireless setup, and a sample conf with comments is included in this folder. NetworkSecurity.txt contains the commands required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
2014-02-14 Breadboard Files
    These files are for the 1.8V Power Supply for the ADC.
2014-02-17 Began work on GPIO communication, including a README and the use of the wiringPi library.
2014-02-22 Pulled arduino OLED code from Tomaž Šolc's git repository as a similar implementation of SPI with a PMOLED.
2014-02-25 Began work on wireless network setup
2014-02-25 Added Python socketing code to new folder.
2014-02-26 add waffle.io badge
2014-02-26 Cloned wiringPi Github repo.
2014-02-26 Additional files added
    Added the following:
    HardwareInterfaces.md for RPi Wireless MACs
    Diagram.vsd: Building block diagram
    RPIConfig.md: Initial startup commands
    Links.txt: Relevant links for AP Setup.
2014-02-26 Added Internationalization Options
2014-02-26 Wireless Config Works.
    After working with the web-server link, RPI2 supports Local Wireless
    Access
2014-02-27 Board 1 2/26
    Increased board size, rotation of RCA & MUX, added connection to I2C,
    room available for DFF's & VCO
2014-02-27 Board Update
    1.8V configured upon approval, D-Flip Flops added (choose optimal), Wire
    configuration still not working correctly
2014-02-27 Update WirelessNetworkSetup.md
    Wireless configuration works, for each Pi perform the following.
2014-02-27 Added directory for I2C
2014-02-28 Board Update 2
    DFF implemented, working on and gates and binary counter
2014-02-28 Board Update 3
    Binary Counter Added, DFF completed, Power Down Resistor added, only
    thing left is to verify unused ADC pins as well as to verify all
    connections are correct (add wires for RPi2 as necessary)
2014-03-02 Basic skeleton code for GPIO to MUX written.
2014-03-03 Began work on RPi2, as well as cleaned up code on RPi1
2014-03-03 Board Update 4
    Update to 1.8V Power Supply, ADC updates, still need ADC finalization as
    well as RCA replacement
2014-03-03 Board Update 4
    Email sent to CUI for RCA Eagle File, RPI 2 female pins added to board,
    ADC pins configured
2014-03-03 Board Update 5
    RCA and Filter still incorrect, all other functions verified and correct
2014-03-03 Board Update 6
    RCA and wire size still incorrect (everything else complete), Filter
    added, ADC correct, Removal of unnecessary wires
2014-03-04 Board Update 7
    Rather than using the TOBU3, I have used a 1x1 pin header and used the
    dimensions of RCJ-32265 (our RCA jack). I also had to move some
    resistors and capacitors around because of the order of input. All else
    remains the same as in 14
2014-03-04 Added wiringPi directory in GPIO
2014-03-04 Rearranged directories into 3 Pi system.
2014-03-05 Clock function temporarily written for functionality
2014-03-05 Board Update Final
    The board is wired (7 mil spacings, GND 21 mil, 18 mil power lines, and
    12 mil regular lines), all spacings/special drill holes correct, ready
    for fabrication
2014-03-05 Configured RPi2 to communicate to the ADC using GPIO.
2014-03-05 Configured RPI2 to communicate to the ADC using I2C.
2014-03-05 SPI functions have been written, will fully integrate once netcode is done.
2014-03-07 Board 1 and 2 Updates
    Board 1 Finalized and Ordered, Board 2 is complete except for Resistors
    for OSCA1 and OSCA2, also Push Bottons need to be replaced
2014-03-08 wiringPi moved, USB mount tutorial added
2014-03-08 3/8/14 Update #2
    Updated USB tutorial, and added basic C client/server from
    http://www.codeproject.com/Articles/586000/Networking-and-Socket-programming-tutorial-in-C
2014-03-08 Socketing finished
    Client-server instantiations work across all three devices, need to now
    implement in broader code.
2014-03-09 Boards Finalized
    All Boards Finalized. Custom Board 2 Changes:
    1) Push Buttons added correctly (temp buttons removed)
    2) GPIO pins initially/always to ground unless button is pressed (3.3 or
    5 V)
    3) Input and Output pins added to board 2_2
    4) Spacing Adjustments
2014-03-09 Board 2 Update
    Switch of Odd and Even Pin Lines
2014-03-10 wiringPi readded.
2014-03-10 SEPS525-OLED-Library added.
2014-03-10 Notes on desired socket implementation.
2014-03-10 Socketing 67% done -- need to work out details with Jake on push-button implementation to determine data format for RPi3 -> RPi2 communication.
2014-03-10 Forgot I2C initalization in setup code.
2014-03-11 Test
2014-03-11 Unsure what the problem is
2014-03-12 Increased Access Point Speed
    Made changes to the hostapd configuration of the wireless access point.
    Now runs a ping test of 40968 bytes at 25ms rather than 120.
2014-04-01 All 3 RPi source codes have been compiled and successfully run on their respective machines. RPi2's I2C protocol will be handled using Python, as the wiringPi I2C code was extremely buggy and did not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
2014-04-08 RPi1 -> RPi3 communication complete
2014-04-29 Added dancing baby bits to directory
2014-04-29 Working with csv library in C
2014-04-29 libcsv untarred.
2014-04-29 Added instance of libcsv to each RPi folder
2014-04-29 Wiringpi change
2014-04-30 RPi3 Update
2014-04-30 CSV Progress
    Added source code for testing a CSV file.
2014-04-30 Individual frame and total GIF parsed using CSV library.
2014-04-30 Added common USB mounting operations.
2014-04-30 Updated networking and CSV code
    Updated RPi1.c to read in CSV frame info rather than relying on Board 1,
    and updated RPi1.c and RPi3.c networking code for operation with Board
    2.
2014-04-30 Updated Makefile
2014-04-30 RPi1.c updated
    CSV should be written on socket now.
2014-05-05 Added libjpeg library for jpeg parsing.
2014-05-05 Wrote files for sending motion data to a framebuffer; motiondetect runs a script in the background to detect when a new JPG appears, motionsend sends said JPG over a TCP connection in 24-bit RGB, and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
2014-05-06 Motion detection script added.
2014-05-07 Code to send JPG across socket added.

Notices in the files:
parts and their libraries:
SparkFun-PowerIC: Licensing: Creative Commons ShareAlike 4.0 International - https://creativecommons.org/licenses/by-sa/4.0
